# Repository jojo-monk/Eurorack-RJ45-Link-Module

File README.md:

# Eurorack-RJ45-Link-Module
Eurorack RJ45 Link Module (Passive)

# 🔌 Eurorack RJ45 Link Module (Passive)

A simple passive Eurorack module that allows you to route up to **8 analog signals** through a single **RJ45 (Ethernet) cable**.

## ✨ Features

- 8 independent signal channels
- Passive design (no power required)
- Uses standard RJ45 / Ethernet cables (Cat5e, Cat6…)
- Compact and easy to build
- Perfect for:
  - Case-to-case signal routing
  - Reducing cable clutter
  - Live performance setups

## 🧠 Concept

This module is essentially a **breakout**:

- Front panel: 8 jack inputs/outputs  
- Rear: RJ45 connector  
- Each jack is directly wired to one conductor of the Ethernet cable  

⚠️ No buffering, attenuation, or protection is included — signals are passed **as-is**.

## 📦 Hardware

### Required components

- 1 × RJ45 connector (through-hole or PCB mount)
- 8 × 3.5mm mono jacks (Thonkiconn or similar)
- PCB (provided in this repo)
- Front panel
- Passive wiring only (no ICs)

### Optional

- Shielded RJ45 connector
- ESD protection (if you want to improve robustness)

## ⚠️ Important Notes

- Eurorack signals can range typically from **-10V to +10V**
- Ethernet cables are not designed for analog modular signals:
  - Possible crosstalk
  - Noise over long distances
- Keep cable lengths reasonable (recommended < 5–10m)

🚫 **Do NOT connect this to network equipment** (switches, routers, computers)

## 🛠️ Build Instructions
[Voir le BOM interactif](https://jojo-monk.github.io/Eurorack-RJ45-Link-Module/bom/ibom.html)
1. Solder the RJ45 connector to the PCB  
2. Solder the 3.5mm jacks  
3. Mount the PCB to the front panel  
4. Verify continuity for all 8 channels  
5. Test with low-level signals first

✅ Tested and fully functional

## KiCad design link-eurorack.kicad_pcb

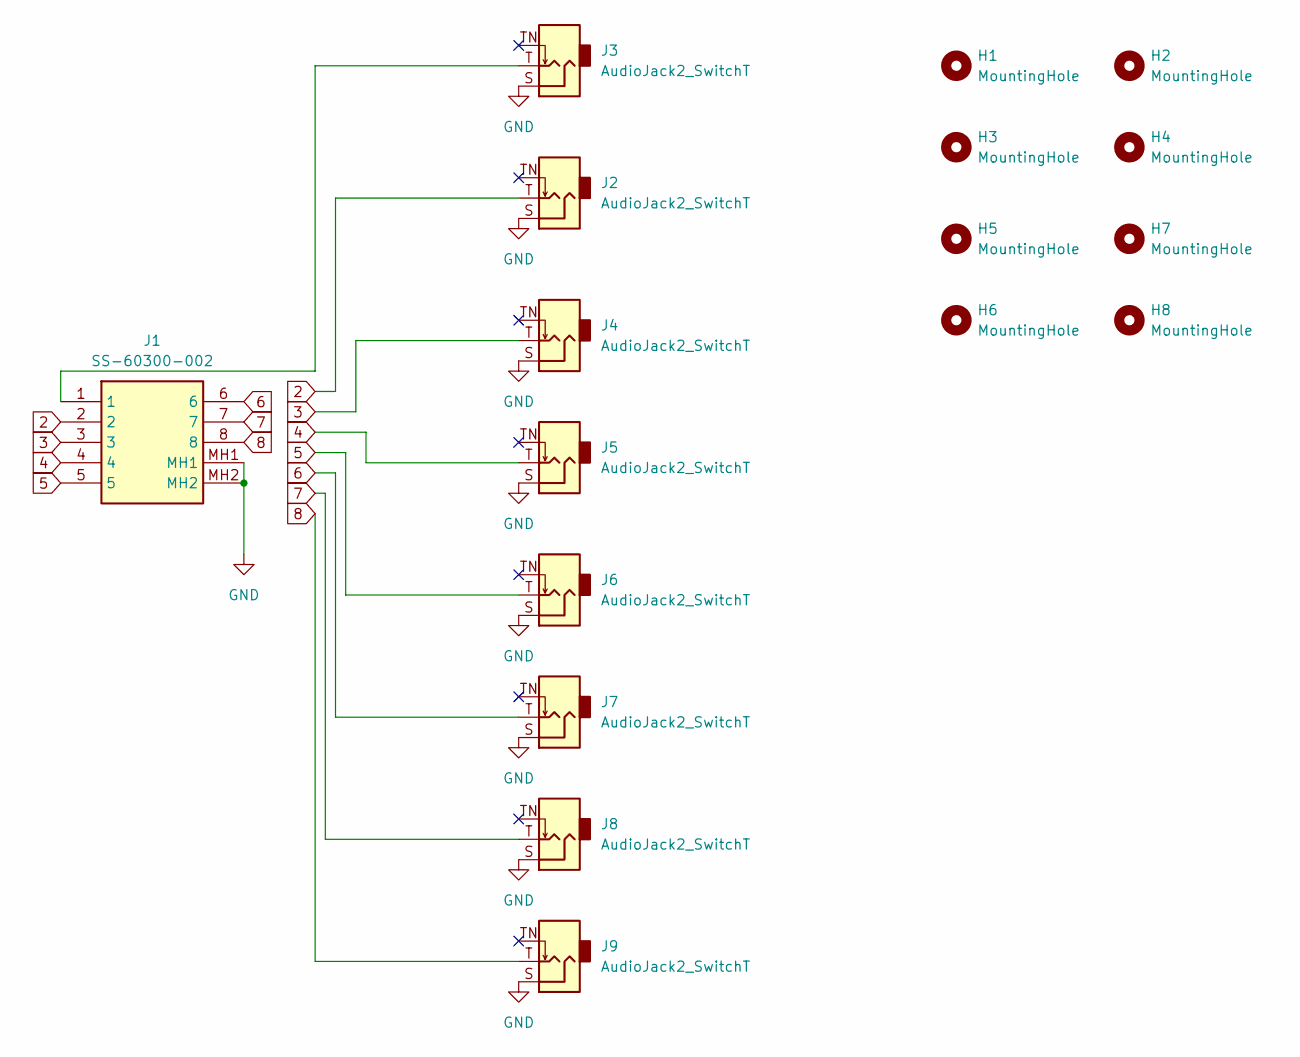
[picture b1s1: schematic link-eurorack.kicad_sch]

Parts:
H1, H2, H3, H4, H5, H6, H7, H8: MountingHole; MountingHole_2.7mm_M2.5
J1: SS-60300-002; SS60300002; Mouser Part Number 530-SS-60300-002
J2, J3, J4, J5, J6, J7, J8, J9: AudioJack2_SwitchT; Jack_3.5mm_QingPu_WQP-PJ398SM_Vertical_CircularHoles

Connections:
2: J1.2, J2.T
3: J1.3, J4.T
4: J1.4, J5.T
5: J1.5, J6.T
6: J1.6, J7.T
7: J1.7, J8.T
8: J1.8, J9.T
GND: J1.MH1, J1.MH2, J2.S, J3.S, J4.S, J5.S, J6.S, J7.S, J8.S, J9.S
unnamed: J1.1, J3.T

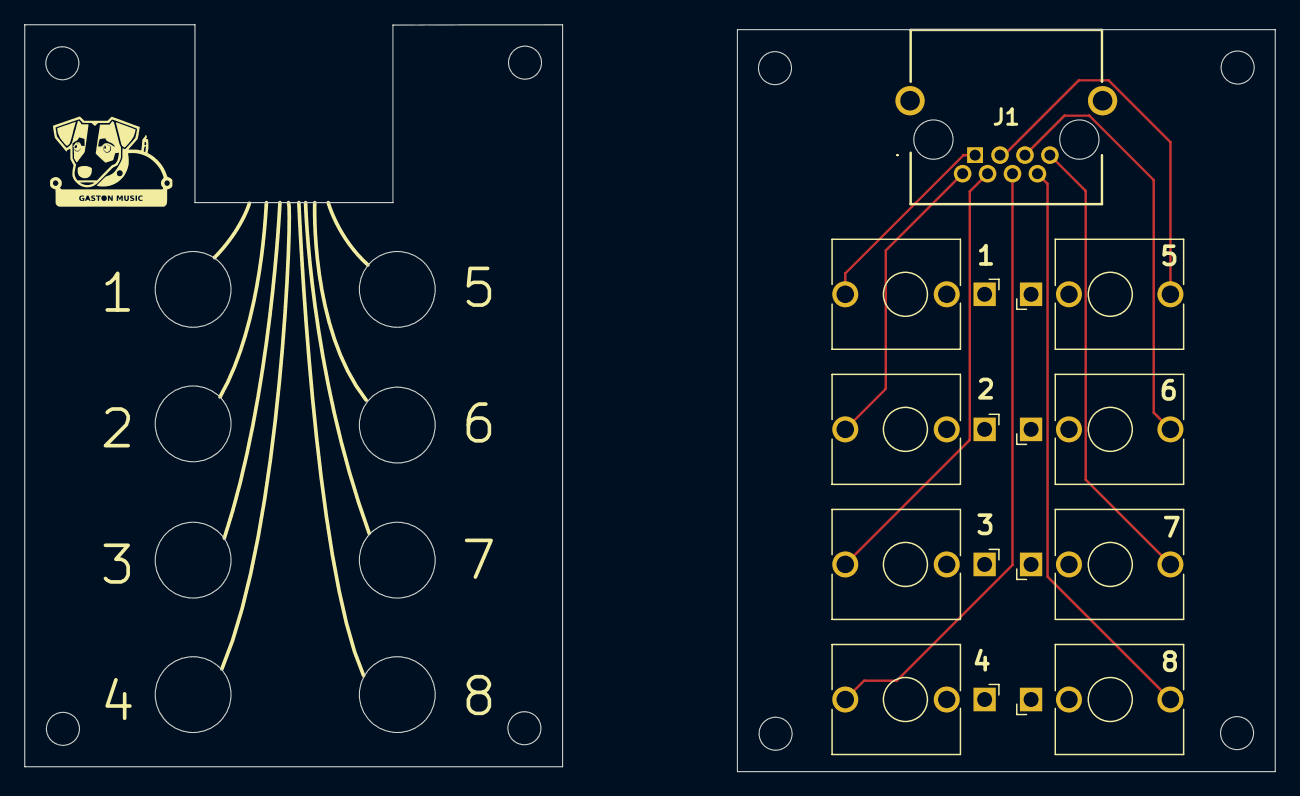
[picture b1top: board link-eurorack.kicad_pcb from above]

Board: 2 copper layers, 44.0 x 60.7 mm, 17 parts (0 on the bottom side), 9 nets.

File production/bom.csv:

Designator,Footprint,Quantity,Value,LCSC Part #
J1,SS60300002,1,SS-60300-002,
"J2, J3, J4, J5, J6, J7, J8, J9",Jack_3.5mm_QingPu_WQP-PJ398SM_Vertical_CircularHoles,8,AudioJack2_SwitchT,

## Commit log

2026-03-31 Enhance README with module details and instructions
    Expanded the README with detailed module features, hardware requirements, pinout, important notes, build instructions, and usage guidelines.
2026-03-31 Remove .DS_Store
2026-03-31 Add interactive BOM link to README
    Added a link to the interactive BOM in the build instructions.
